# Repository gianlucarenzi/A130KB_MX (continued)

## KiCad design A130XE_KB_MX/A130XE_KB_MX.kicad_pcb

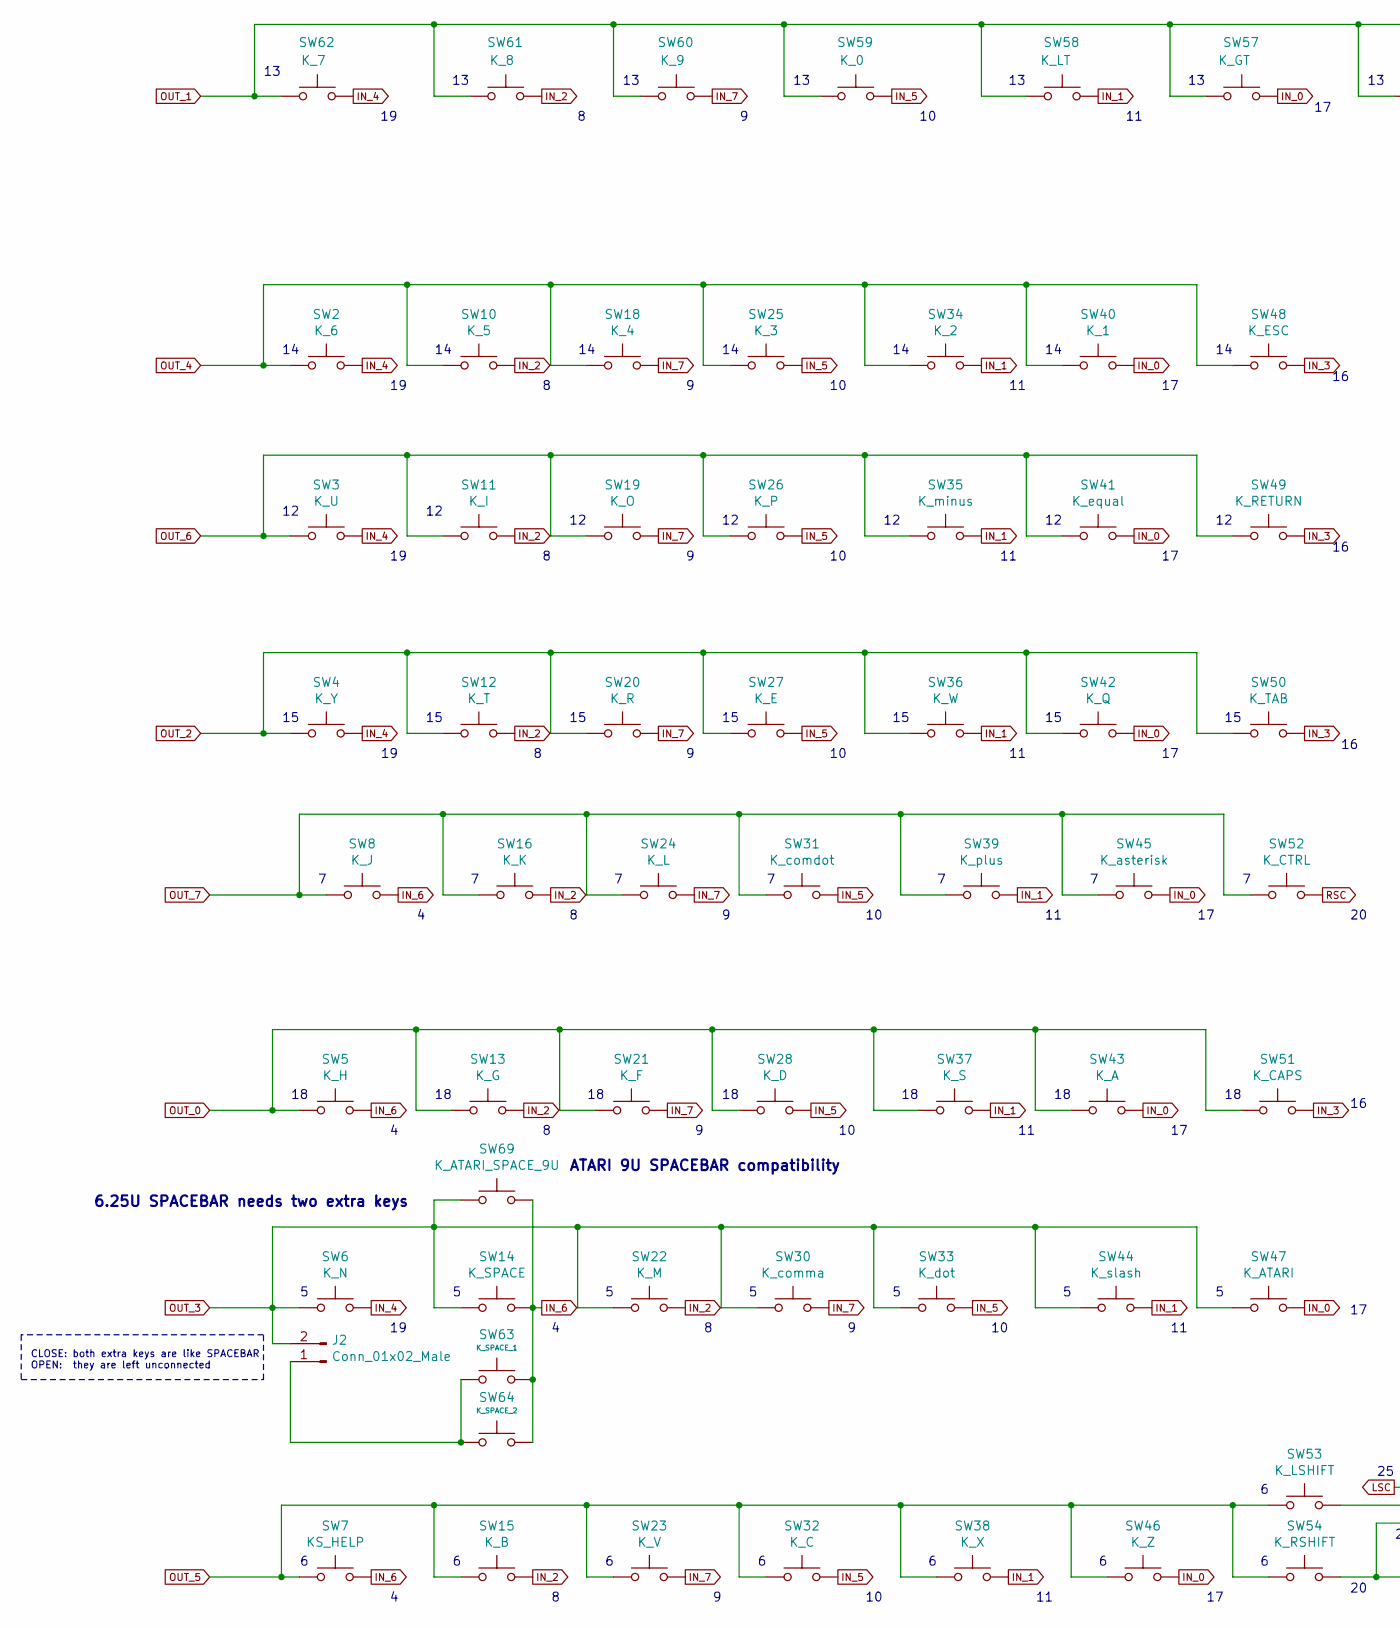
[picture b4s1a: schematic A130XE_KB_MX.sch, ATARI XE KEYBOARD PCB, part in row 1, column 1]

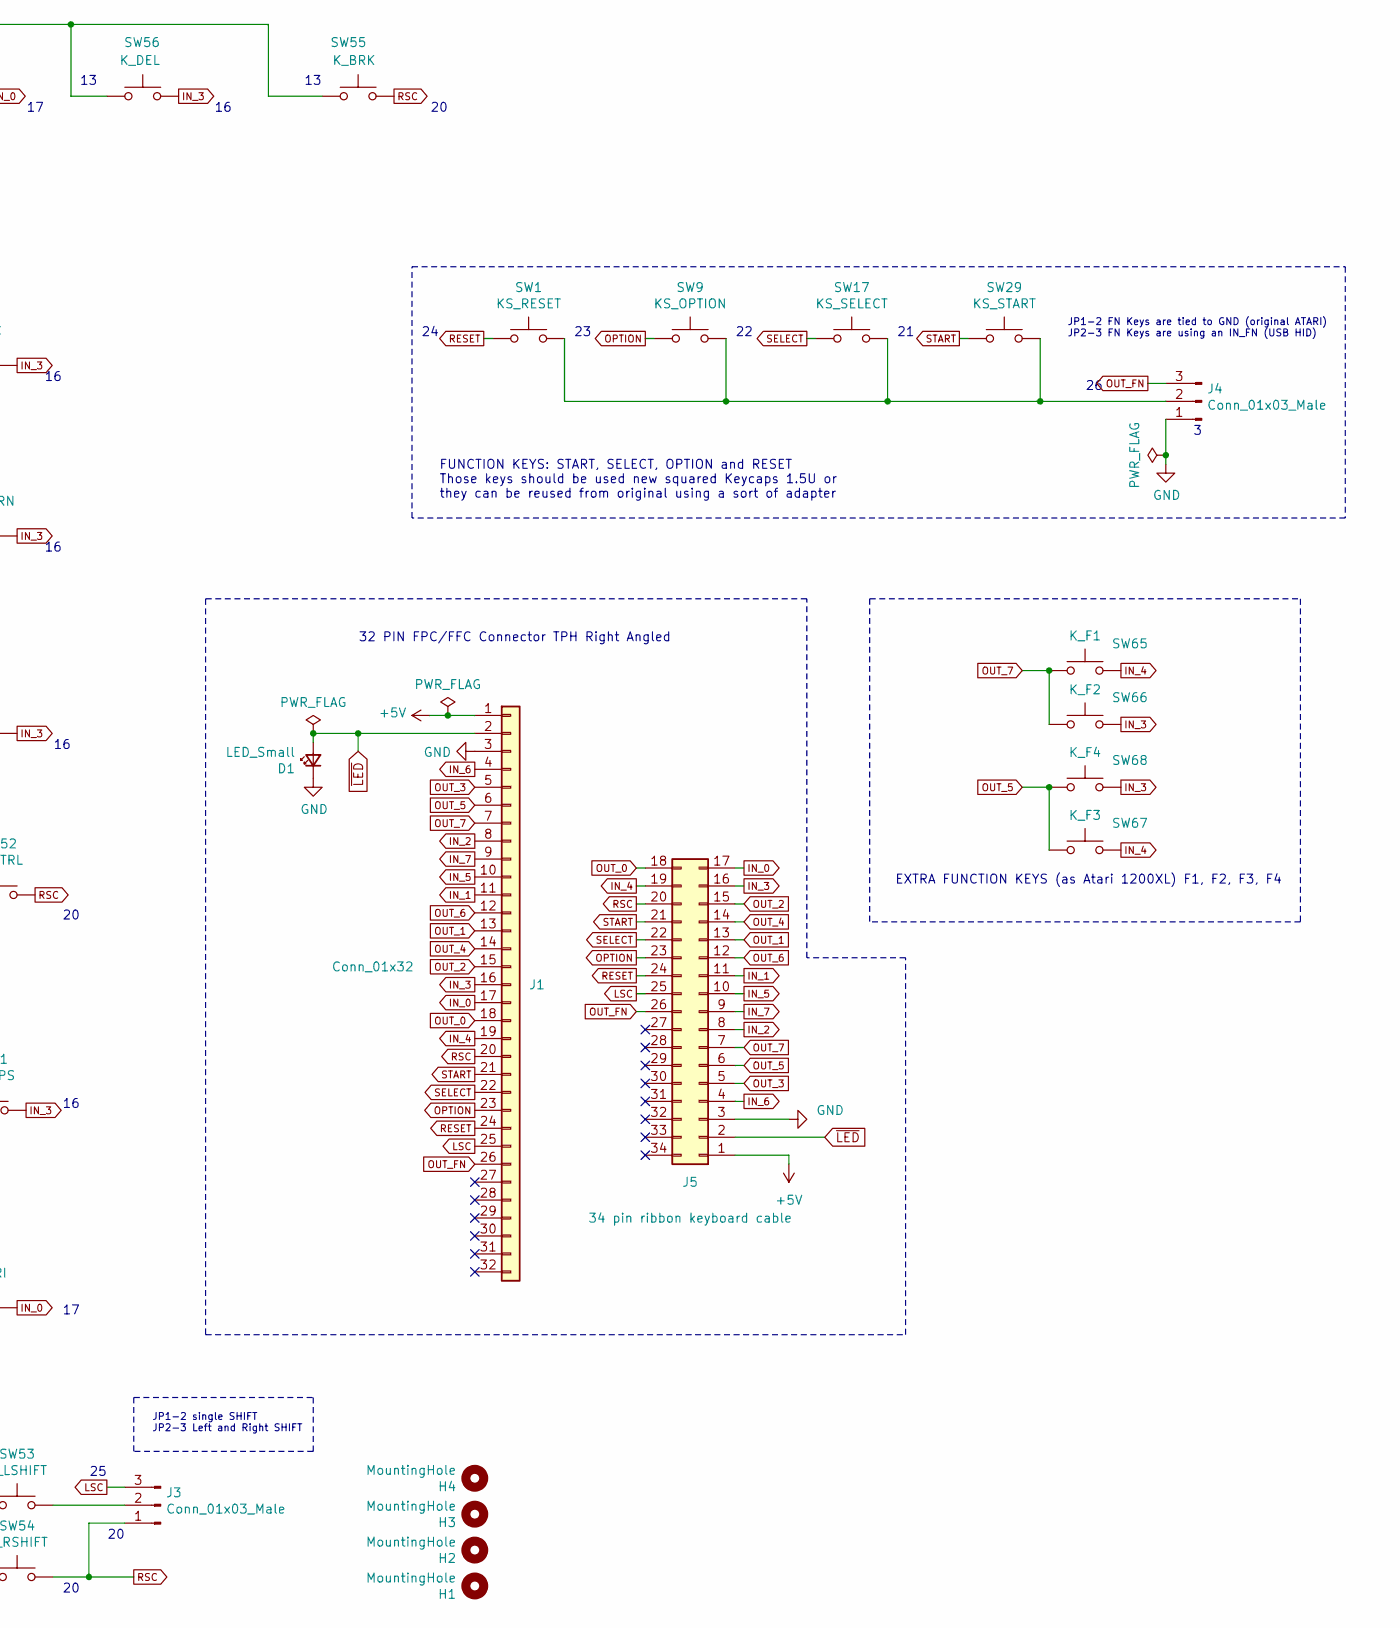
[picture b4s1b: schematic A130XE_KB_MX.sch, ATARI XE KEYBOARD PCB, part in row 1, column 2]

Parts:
D1: LED_Small; LED_1210_3225Metric_Pad1.42x2.65mm_HandSolder
H1, H2, H3, H4: MountingHole; MountingHole_3.7mm
J1: Conn_01x32; MOLEX-FFC-1.25mm-RA-52044-3245
J2: Conn_01x02_Male; PinHeader_1x02_P2.54mm_Vertical
J3, J4: Conn_01x03_Male; PinHeader_1x03_P2.54mm_Vertical
J5: 34 pin ribbon keyboard cable; IDC-Header_2x17_P2.54mm_Vertical
SW1: KS_RESET; SW_Cherry_MX1A_1.50u_ATARI_XE_PCB_3d
SW2: K_6; SW_Cherry_MX1A_1.00u_PCB_3d
SW3: K_U; SW_Cherry_MX1A_1.00u_PCB_3d
SW4: K_Y; SW_Cherry_MX1A_1.00u_PCB_3d
SW5: K_H; SW_Cherry_MX1A_1.00u_PCB_3d
SW6: K_N; SW_Cherry_MX1A_1.00u_PCB_3d
SW7: KS_HELP; SW_Cherry_MX1A_1.50u_ATARI_XE_PCB_3d
SW8: K_J; SW_Cherry_MX1A_1.00u_PCB_3d
SW9: KS_OPTION; SW_Cherry_MX1A_1.50u_ATARI_XE_PCB_3d
SW10: K_5; SW_Cherry_MX1A_1.00u_PCB_3d
SW11: K_I; SW_Cherry_MX1A_1.00u_PCB_3d
SW12: K_T; SW_Cherry_MX1A_1.00u_PCB_3d
SW13: K_G; SW_Cherry_MX1A_1.00u_PCB_3d
SW14: K_SPACE; SW_Cherry_MX1A_6.25u_PCB_3d
SW15: K_B; SW_Cherry_MX1A_1.00u_PCB_3d
SW16: K_K; SW_Cherry_MX1A_1.00u_PCB_3d
SW17: KS_SELECT; SW_Cherry_MX1A_1.50u_ATARI_XE_PCB_3d
SW18: K_4; SW_Cherry_MX1A_1.00u_PCB_3d
SW19: K_O; SW_Cherry_MX1A_1.00u_PCB_3d
SW20: K_R; SW_Cherry_MX1A_1.00u_PCB_3d
SW21: K_F; SW_Cherry_MX1A_1.00u_PCB_3d
SW22: K_M; SW_Cherry_MX1A_1.00u_PCB_3d
SW23: K_V; SW_Cherry_MX1A_1.00u_PCB_3d
SW24: K_L; SW_Cherry_MX1A_1.00u_PCB_3d
SW25: K_3; SW_Cherry_MX1A_1.00u_PCB_3d
SW26: K_P; SW_Cherry_MX1A_1.00u_PCB_3d
SW27: K_E; SW_Cherry_MX1A_1.00u_PCB_3d
SW28: K_D; SW_Cherry_MX1A_1.00u_PCB_3d
SW29: KS_START; SW_Cherry_MX1A_1.50u_ATARI_XE_PCB_3d
SW30: K_comma; SW_Cherry_MX1A_1.00u_PCB_3d
SW31: K_comdot; SW_Cherry_MX1A_1.00u_PCB_3d
SW32: K_C; SW_Cherry_MX1A_1.00u_PCB_3d
SW33: K_dot; SW_Cherry_MX1A_1.00u_PCB_3d
SW34: K_2; SW_Cherry_MX1A_1.00u_PCB_3d
SW35: K_minus; SW_Cherry_MX1A_1.00u_PCB_3d
SW36: K_W; SW_Cherry_MX1A_1.00u_PCB_3d
SW37: K_S; SW_Cherry_MX1A_1.00u_PCB_3d
SW38: K_X; SW_Cherry_MX1A_1.00u_PCB_3d
SW39: K_plus; SW_Cherry_MX1A_1.00u_PCB_3d
SW40: K_1; SW_Cherry_MX1A_1.00u_PCB_3d
SW41: K_equal; SW_Cherry_MX1A_1.00u_PCB_3d
SW42: K_Q; SW_Cherry_MX1A_1.00u_PCB_3d
SW43: K_A; SW_Cherry_MX1A_1.00u_PCB_3d
SW44: K_slash; SW_Cherry_MX1A_1.00u_PCB_3d
SW45: K_asterisk; SW_Cherry_MX1A_1.00u_PCB_3d
SW46: K_Z; SW_Cherry_MX1A_1.00u_PCB_3d
SW47: K_ATARI; SW_Cherry_MX1A_1.00u_PCB_3d
SW48: K_ESC; SW_Cherry_MX1A_1.00u_PCB_3d
SW49: K_RETURN; SW_Cherry_MX1A_1.50u_PCB_3d
SW50: K_TAB; SW_Cherry_MX1A_1.50u_PCB_3d
SW51: K_CAPS; SW_Cherry_MX1A_1.25u_PCB_3d
SW52: K_CTRL; SW_Cherry_MX1A_1.75u_PCB_3d
SW53: K_LSHIFT; SW_Cherry_MX1A_2.25u_PCB_3d
SW54: K_RSHIFT; SW_Cherry_MX1A_1.75u_PCB_3d
SW55: K_BRK; SW_Cherry_MX1A_1.00u_PCB_3d
SW56: K_DEL; SW_Cherry_MX1A_1.00u_PCB_3d
SW57: K_GT; SW_Cherry_MX1A_1.00u_PCB_3d
SW58: K_LT; SW_Cherry_MX1A_1.00u_PCB_3d
SW59: K_0; SW_Cherry_MX1A_1.00u_PCB_3d
SW60: K_9; SW_Cherry_MX1A_1.00u_PCB_3d
SW61: K_8; SW_Cherry_MX1A_1.00u_PCB_3d
SW62: K_7; SW_Cherry_MX1A_1.00u_PCB_3d
SW63: K_SPACE_1; SW_Cherry_MX1A_1.25u_PCB_3d
SW64: K_SPACE_2; SW_Cherry_MX1A_1.50u_PCB_3d
SW65: K_F1; SW_Cherry_MX1A_1.00u_PCB_3d
SW66: K_F2; SW_Cherry_MX1A_1.00u_PCB_3d
SW67: K_F3; SW_Cherry_MX1A_1.00u_PCB_3d
SW68: K_F4; SW_Cherry_MX1A_1.00u_PCB_3d
SW69: K_ATARI_SPACE_9U; SW_Cherry_MX1A_9u_PCB_3d

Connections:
+5V: J1.1, J5.1
GND: D1.1 (K), J1.3, J4.1, J5.3
IN_0: J1.17, J5.17, SW40.2, SW41.2, SW42.2, SW43.2, SW45.2, SW46.2, SW47.2, SW57.2
IN_1: J1.11, J5.11, SW34.2, SW35.2, SW36.2, SW37.2, SW38.2, SW39.2, SW44.2, SW58.2
IN_2: J1.8, J5.8, SW10.2, SW11.2, SW12.2, SW13.2, SW15.2, SW16.2, SW22.2, SW61.2
IN_3: J1.16, J5.16, SW48.2, SW49.2, SW50.2, SW51.2, SW56.2, SW66.2, SW68.2
IN_4: J1.19, J5.19, SW2.2, SW3.2, SW4.2, SW6.2, SW62.2, SW65.2, SW67.2
IN_5: J1.10, J5.10, SW25.2, SW26.2, SW27.2, SW28.2, SW31.2, SW32.2, SW33.2, SW59.2
IN_6: J1.4, J5.4, SW5.2, SW7.2, SW8.2, SW14.2, SW63.2, SW64.2, SW69.2
IN_7: J1.9, J5.9, SW18.2, SW19.2, SW20.2, SW21.2, SW23.2, SW24.2, SW30.2, SW60.2
LSC: J1.25, J3.3, J5.25
unnamed: J2.1, SW63.1, SW64.1
unnamed: J3.2, SW53.2
unnamed: J4.2, SW1.2, SW9.2, SW17.2, SW29.2
OPTION: J1.23, J5.23, SW9.1
OUT_0: J1.18, J5.18, SW5.1, SW13.1, SW21.1, SW28.1, SW37.1, SW43.1, SW51.1
OUT_1: J1.13, J5.13, SW55.1, SW56.1, SW57.1, SW58.1, SW59.1, SW60.1, SW61.1, SW62.1
OUT_2: J1.15, J5.15, SW4.1, SW12.1, SW20.1, SW27.1, SW36.1, SW42.1, SW50.1
OUT_3: J1.5, J2.2, J5.5, SW6.1, SW14.1, SW22.1, SW30.1, SW33.1, SW44.1, SW47.1, SW69.1
OUT_4: J1.14, J5.14, SW2.1, SW10.1, SW18.1, SW25.1, SW34.1, SW40.1, SW48.1
OUT_5: J1.6, J5.6, SW7.1, SW15.1, SW23.1, SW32.1, SW38.1, SW46.1, SW53.1, SW54.1, SW67.1, SW68.1
OUT_6: J1.12, J5.12, SW3.1, SW11.1, SW19.1, SW26.1, SW35.1, SW41.1, SW49.1
OUT_7: J1.7, J5.7, SW8.1, SW16.1, SW24.1, SW31.1, SW39.1, SW45.1, SW52.1, SW65.1, SW66.1
OUT_FN: J1.26, J4.3, J5.26
RESET: J1.24, J5.24, SW1.1
RSC: J1.20, J3.1, J5.20, SW52.2, SW54.2, SW55.2
SELECT: J1.22, J5.22, SW17.1
START: J1.21, J5.21, SW29.1
~LED: D1.2 (A), J1.2, J5.2

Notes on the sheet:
EXTRA FUNCTION KEYS (as Atari 1200XL) F1, F2, F3, F4
FUNCTION KEYS: START, SELECT, OPTION and RESET Those keys should be used new squared Keycaps 1.5U or they can be reused from original using a sort of adapter
JP1-2 single SHIFT JP2-3 Left and Right SHIFT
JP1-2 FN Keys are tied to GND (original ATARI) JP2-3 FN Keys are using an IN_FN (USB HID)
CLOSE: both extra keys are like SPACEBAR OPEN: they are left unconnected
32 PIN FPC/FFC Connector TPH Right Angled
ATARI 9U SPACEBAR compatibility
6.25U SPACEBAR needs two extra keys

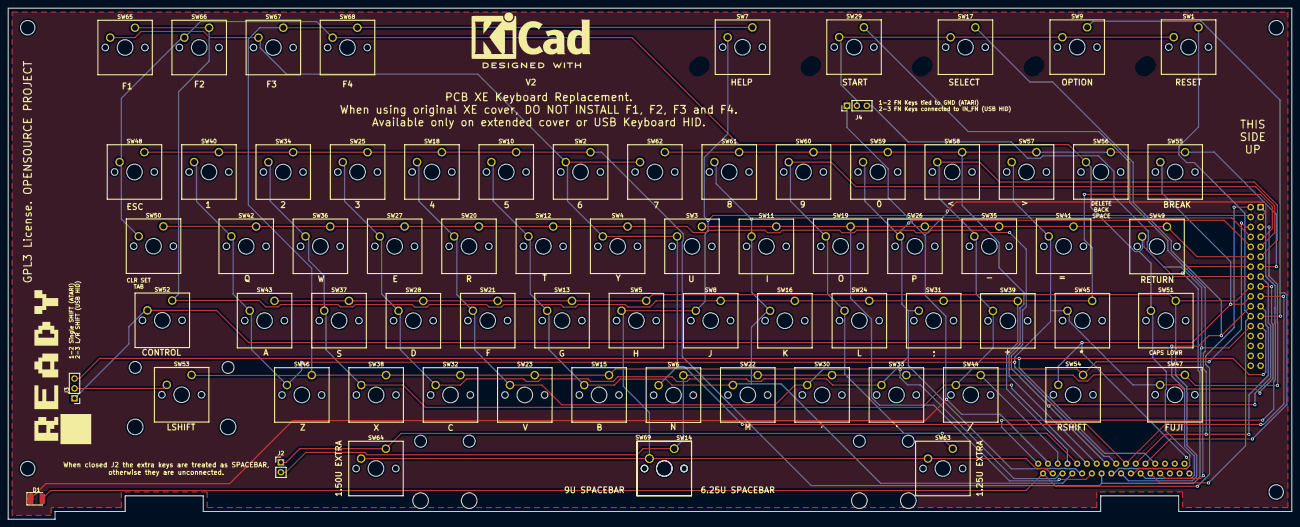
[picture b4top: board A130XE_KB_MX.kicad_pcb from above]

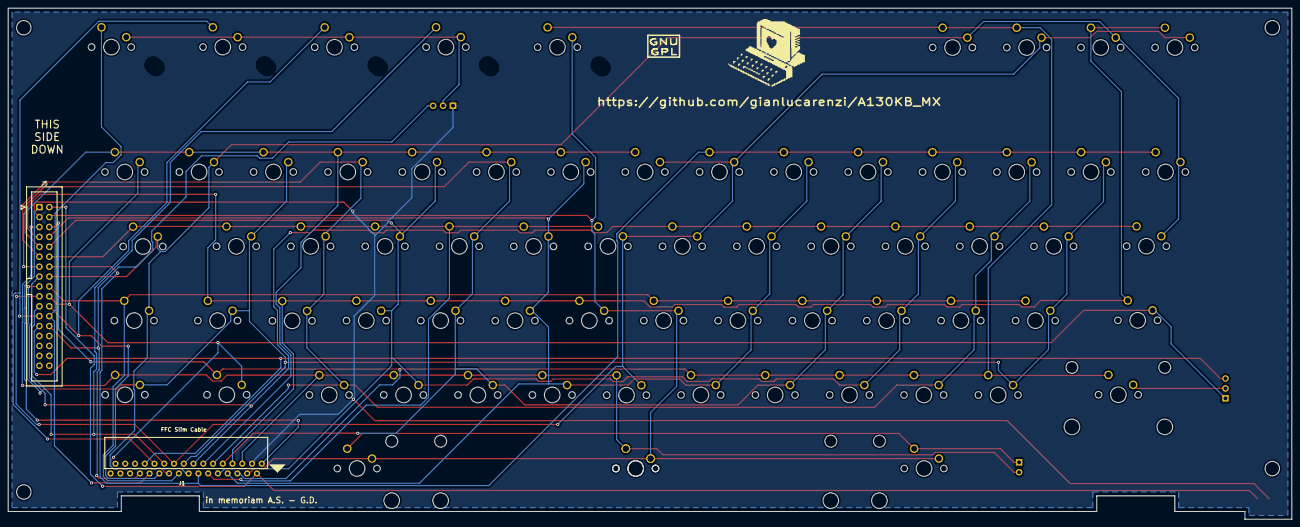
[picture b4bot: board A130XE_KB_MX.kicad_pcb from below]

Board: 2 copper layers, 329.0 x 131.0 mm, 81 parts (3 on the bottom side), 29 nets.

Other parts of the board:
GNUGPL: Symbol_GNU-GPL_CopperTop_Small; Symbol_GNU-GPL_SilkScreen_Small
READY: LOGO; atari_ready_14mm_rev

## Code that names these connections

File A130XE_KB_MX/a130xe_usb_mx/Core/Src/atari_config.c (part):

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};

gpioPort_t lut_row[ KEYBOARD_ROWS ] = {
	{ .port = ROW0_GPIO_Port, .pin = ROW0_Pin },
	{ .port = ROW1_GPIO_Port, .pin = ROW1_Pin },
	{ .port = ROW2_GPIO_Port, .pin = ROW2_Pin },
	{ .port = ROW3_GPIO_Port, .pin = ROW3_Pin },
	{ .port = ROW4_GPIO_Port, .pin = ROW4_Pin },
	{ .port = ROW5_GPIO_Port, .pin = ROW5_Pin },
	{ .port = ROW6_GPIO_Port, .pin = ROW6_Pin },
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};

gpioPort_t lut_col[ KEYBOARD_COLUMNS ] = {
	{ .port = COL0_GPIO_Port,  .pin = COL0_Pin },
	{ .port = COL1_GPIO_Port,  .pin = COL1_Pin },
	{ .port = COL2_GPIO_Port,  .pin = COL2_Pin },
	{ .port = COL3_GPIO_Port,  .pin = COL3_Pin },
	{ .port = COL4_GPIO_Port,  .pin = COL4_Pin },
	{ .port = COL5_GPIO_Port,  .pin = COL5_Pin },
	{ .port = COL6_GPIO_Port,  .pin = COL6_Pin },
	{ .port = COL7_GPIO_Port,  .pin = COL7_Pin },
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	// D2: SCROLL lock
	// D3: Compose
	// D4: Kana
	const char * LED[5] = {"NUM lock", "CAPS lock", "SCROLL lock", "Compose", "Kana", };

	int i;
	unsigned char * ptr = (unsigned char *) report;
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
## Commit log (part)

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2020-10-11 First import
2020-10-12 ignored
2020-10-19 New files for reversed Row descriptions for MaxKeyboards
2020-10-19 New layout for spacebar 6.25 and two 1.25 at side. Function keys are 1.5u.
2020-10-20 added json layout for both systems: 800XL/600XL and Atari 800
2020-10-20 Correct of some keycap sizes. The spacebar is now 6.25u. The layout should be compatible with Atari 800 and Atari 800XL/600XL. The PCB will vary from 800 and XL series.
2020-10-20 Left Shift's legend was too far off the center.
2020-10-23 Added the wonderful font Gorton Digital! I love it!
2020-10-23 Original Atari Logo. It's Copyrighted!
2020-10-23 Fonts created by SourceForge and converted from OTF to TTF (as Inkscape seems not to working with OTF style fonts!)
2020-10-23 Original Atari Fuji Logo
2020-10-23 First Layout for PC 104 ANSI Keyboard
2020-10-23 Better text size. Numeric Keypad like CX85
2020-10-23 First usage
2020-10-23 Added some MacOS files to be ignored
2020-10-23 Repositioned some non centered legends. First usage with MacOS X & XQuartz
2020-10-24 PC 104 Atari XE Style
2020-10-24 The arrows were reversed
2020-10-24 Finished ATARI 800 Style PC 104 ANSI Keyboard
2020-10-29 First import (ISO & ANSI Layout)
2020-10-29 Updated for ANSI/ISO Layout and some corrections
2020-11-08 Added mechanics for XL (next project)
2020-11-08 Atari XL only project. Drop Atari 800 support due to lack of information about keyboard PCB size and measurements. Now having an Atari XL the measurements should be ok.
2020-11-09 Updated for well centered legends, and modified keycaps around the spacebar to fit 9U size and *NOT* 8.75U as Atari 800 keyboard size (now dropped)
2020-11-09 The spacebar should be 9u and not 8.75u. So one of the surrounded keys must be 1.5u and not 1.25u. The PCB must be modified accordingly
2020-11-10 Changed layout of buttons surrounding the spacebar. Atari XE seems to have 9U spacebar, so we are using 6.25u (more common) and two keys around it (1.25u and 1.50u)
2020-11-10 Correct user: debian
2020-11-10 Added ROW indicators on the right too.
2020-11-10 Modified the CAPS LOWR keycap.
2020-11-11 Generated on my home computer
2020-11-17 Added for print as stickers
2020-11-17 Some keys legends were NOT white
2020-11-17 Removed duplicate cut contours. Corrected layout for cutting. Some legends were too much close to the cutting edge.
2020-11-21 Added
2020-11-21 It was too big. With a paper board it was too near the keyboard assy. Now it's as small as possible.
2020-11-21 Added silkscreen print for spacebar sizes
2020-12-23 Added png of layouts. Some AliExpress/AliBaba ask for images
2020-12-24 Color change due to the RAL Colors Code and a real 800XL. It looks like the Case color and the Keycaps colors are RAL 8019. Ambient light K7000 and led lights. Between dark brown and blackishy. RAL 8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
2020-12-29 Added new footprints for keys (with 3D WRL and Stabilizers where needed)
2020-12-29 Generated after a strange warning on JLCPCB which gave me 4 layers!! :-/
2020-12-29 Adapted for new positioning and removed error DRC on PCB
2020-12-29 Modified
2020-12-29 Sent to JLCPCB 2020-12-29
2021-01-03 First import of Keyboard USB Controller
2021-01-05 Ignore the result of the build.
2021-01-05 Added the 3 lines for Amiga Compatibility
2021-01-09 First import from tmk_keyboard
2021-01-10 Integration with other modules from TMK Keyboard
2021-01-10 Change variable name and type. Now it is an array for Alternate Functions
2021-01-10 Modified for usage with STM32Lib
2021-01-10 added Binary Printf
2021-01-12 Avoid print every time all alternates matrix. Only a single row @ time.
2021-01-29 Added Function Keys in the layout. SVG is not generated as it is useful as is.
2021-01-29 Rebuilt from another web source: http://www.keyboardcad.com
2021-01-29 Regenerated after V2 (HELP, START, ..., RESET) are created from json file too. New plate & build web service with: http://www.keyboardcad.com
2021-01-29 Generated from Schematics' Plot
2021-01-30 F3 and F4 were inverted. Now they works fine. Thanks to OS ROM SELF-TEST Keyboard test.
2021-02-01 Updated with two jumpers for: 1- SHIFT ATARI (single shift) * DEFAULT 1-2 2- USB HID LSHIFT & RSHIFT 2-3
2021-02-01 Updated for a review to JLCPCB
2021-02-02 Added some pictures and SVG for e-mail explanation. The jpg files are from Xad Dave NightFall Crew site! Thanks dude!
2021-02-02 Added some text into schematics. Renamed IN_FN as OUT_FN as it is an OUTPUT from microprocessor point of view.
2021-02-02 Removed as they are actually useless
2021-02-02 Latest JLCPCB Gerber files. They looks ok to me
2021-02-02 Updated some text schematics information
2021-02-07 With new Kicad 5.1 those files are renamed
2021-02-07 Renamed with Kicad 5.1
2021-02-07 New FPC cable. No Flat Ribbon. It was too big!
2021-02-07 No use
2021-02-07 New FPC cable. The Flat ribbon is for external USB HID Keyboard
2021-03-11 Updated connector name
2021-03-14 - 12mm x 12mm sticker size - Bold Font for reverse legends - slightly modified Atari Fuji Logo Key for better printing
2021-03-14 The reverse lagends are little bit smaller, more or less like the original ATARI 800XL Keycaps.
2021-03-16 All keycaps in DSA Profile
2021-03-16 Removed duplicate cut contours. Corrected layout for cutting. Now cut contours are 12 x 12 mm and they fit in almost every keycap. The cutcontour color should be RGB FF00FF or CMYK 0 100% 0 0 For the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
2021-03-16 Genrated on MacOSX with Inkscape for Mac
2021-03-24 New layout. The spacebar is moved a little to the right, so the extra two keys are inverted to fit the computer plastic case hole.
2021-03-24 First BOM
2021-03-24 New plots for new layout
2021-03-25 Modified the spacebar layout. Now it is a 8.75U (6.25U + 2 x 1.25U)
2021-03-26 Inverted the extra keys (1.25U and 1.50U) to permit the space-bar a 0.25U best-fit to the right.
2021-03-26 Updated to reflect the new keycaps position for spacebar and the other extra 2 keys around it.
2021-03-26 Cleanup the extra unsused layers for Drawings.
2021-03-26 Rules after autorouting
2021-03-29 Added Cherry MX catalogue and codes
2021-04-03 New render for extra hole in the function keys (even if not needed really) and the spacebar 9U as alternative for modern spacebar 6.25U plus the other two keys
2021-04-05 Updated for PCB Production for JLCPCB Apr.5th 2021
2021-04-05 Updated for PCB Production for JLCPCB Apr.5th 2021.
2021-04-14 Added 3D print stackpoles for Atari XE and ATARI XL (I know there are some other keyboards for XE and XL)
2021-04-14 Added other stackpole/stems for the other Atari XE keyboard I own.
2021-05-01 Include missing for Eclipse
2021-05-01 More compact serial debug
2021-05-01 Added C_DEFS and added a make flash command
2021-05-01 Rearranged for COLUMS and ROWS
2021-05-01 Try with NO GHOSTING on Atari... :-/
2021-05-01 Eclipse files
2021-05-02 Added some debug information on level
2021-05-02 trailing blank spaces
2021-05-02 Added debug information on level
2021-05-02 ATARI KEYMAP IS REVERSED (switch ROWS with COLUMNS)
2021-05-02 debug
2021-05-02 USB Driver registered into TMK Keyboard Driver Setup
2021-05-02 Modified for no output debug
2021-05-02 Added USB callback and BACKSPACE instead of DELETE GT and LT does not work properly. It's a matter of configuration stuff. They are sent as report HID USB but the driver does not care about them, lik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
2021-05-02 Added comment
2021-05-03 Added support for 2 endpoints, one for sending and one for reading leds
2021-05-03 welcome led splash
2021-05-03 autogenerated
2021-12-02 During poweron all leds are blinking
2021-12-02 Added leds for: CAPS LOCK, SCROLL LOCK, NUM LOCK, COMPOSE and KANA
2021-12-02 Leds management. Up to 5 leds
2021-12-10 First attempt (not finished yet) to adapt some standard ATARI Layout keyboard out-there! ;-)
2021-12-21 Moved from 3d-junkyard
2021-12-29 Adapted for real keyboard. Both shift were different.
2021-12-29 Added for USB Keyboard
2021-12-29 Added CSV
2021-12-29 BUG for LALT & RALT when used in Atari mode. Wrong ROW8 it must be ROW7 Tracks size increased, expecially for GND/POWER signals Added 9U spacebar and stabilizers like Atari keycaps. This is PCB only.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
2021-12-29 Updated for new PCB
2021-12-29 Removed
2021-12-29 Updated for References
2021-12-29 Corrected for DRC Rule Checker
2021-12-29 Committed. Dunno if they are needed.
2021-12-29 Added for CAD Files
2021-12-31 Removed. Not needed in Git
2021-12-31 Added extra holes for 6.25U, 9U and stabilizers holes
2021-12-31 New drill files for Plate
2021-12-31 Added extra holes for 6.25U, 9U and stabilizers holes. Added extra holes for mounting on top cover if exist.
2021-12-31 Interactive BOM
2021-12-31 Added for extra holes on spacebar and stabilizers
2022-01-08 Updated to reflect latest libraries
2022-01-12 Created for better InkScape overlay
2022-01-12 Using Atari spacebar (not fully 9U lenght). Other keys layout must be adapted a little bit.
2022-01-12 Must be finished. It does not work
2022-01-12 It's simpler to use a (almost) standard 7U spacebar and two 1u extra keys. In that way, the holes needed are only for extra 9U stabilizers.
2022-01-12 It's simpler to use a (almost) standard 7U spacebar and two 1u extra keys. In that way, the holes needed are only for extra 9U stabilizers. Even the plate gets simpler.
2022-01-21 New STM32CubeMX format
2022-01-21 Removed the original FFC connector. This will lose any compatibility between two projects
2022-01-30 Updated sizes for R1 (shift) and spacebar 7U
2022-02-04 FreeCad Project for plate and PCB (with all keys). Stabilizers are missing... :-(
2022-02-04 New export
2022-02-04 Updated to reflect the correct path for importing the PCB in FreeCad with the KicadStepUp plugin
2022-02-04 New mechanical step object with PCB, Plate, Connectors, RasPi Pico and switches. Stabilizers are missing
2022-02-04 Ignore some more files
2022-02-05 Sent to JLCPCB
2022-02-09 Added 3D shape of the keycap
2022-02-09 Updated PCB for 3D models
2022-02-09 Updated footprint library cache. Not really needed
2022-02-10 Switches with no 3D Switch. They are much lighter for rendering.
2022-02-10 Changed from switches with 3D CherryMX Switch, to switches with only the keycaps. They are much lighter for renderings The PCB should not be affected, but I redo a Plot just for sure.
2022-02-17 Create on Adobe Illustrator on a MacOS X Computer
2022-02-17 Imported from AI then modified with InkScape in Linux.
2022-02-17 Created as EPS for stickers printing
2022-02-17 Updated with the correct cut-contour size 12mm x 12mm as 1U
2022-02-17 Convertiti in PDF con e senza font. Vediamo quale si adatta al lavoro...
2022-02-17 Aggiornato con le dimensioni corrette di CAPS LOCK. Era troppo piccolo e puo' non coprire la scritta completa sotto...
2022-02-21 First attempt for waterslide decals
2022-02-21 Added a layer as Original Atari XE Font
2022-02-21 Reversed for WaterSlide Decals printing. Added all semigraphics symbols. They should be printed on front side of the keycap
2022-02-24 Modified the 3D object for the function keys. The overall should not be affected (need to be confirmed)
2022-03-13 Straight vertical Molex Connector: RA52045-3245 (End Of Life!!)
2022-03-13 The height of the board is very tight with the PCB installed. It needs to be at maximum of 12.3mm, so use a vertical (so become angled) connector. The original connector can be used but with a keyboa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
2022-03-13 The height of the board is very tight with the PCB installed. It needs to be at maximum of 12.3mm, so use a vertical (so become angled) connector. The original connector can be used but with a keyboa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
2022-03-13 JLCPCB Mar 13th 2022: 30pcs
2022-05-09 Revised the used font: now only Gorton Digital (Regular)
2022-05-25 Low profile
2022-05-31 Added for a standard layout Atari 800 Style PC-Keyboard (ISO and ANSI) Added all non-standard Atari keys for easier replacement of those keyboards (800, 600XL, 800XL and 1200XL [TBD]) Added some fanc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
2022-06-07 Color correction
2022-06-14 Added all needed keys for PC ISO/ANSI, Original Atari XL (keyboard replacement PCB needed), Original Atari XE (keyboard replacement PCB needed). All in Atari 800 color variant.
2022-06-17 Updated with the final setup
2022-06-19 Removed 2.5u shift because it's not available anymore Changed to 2.25u and 2u to fill the gap. Added the 1.5u CTRL as Atari 800 original CTRL
2022-08-27 Corrected with the three stems adapter
2022-12-03 Optimized with only a single call
